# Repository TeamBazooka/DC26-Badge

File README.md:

# DC26 Team Bazooka

Figure it out

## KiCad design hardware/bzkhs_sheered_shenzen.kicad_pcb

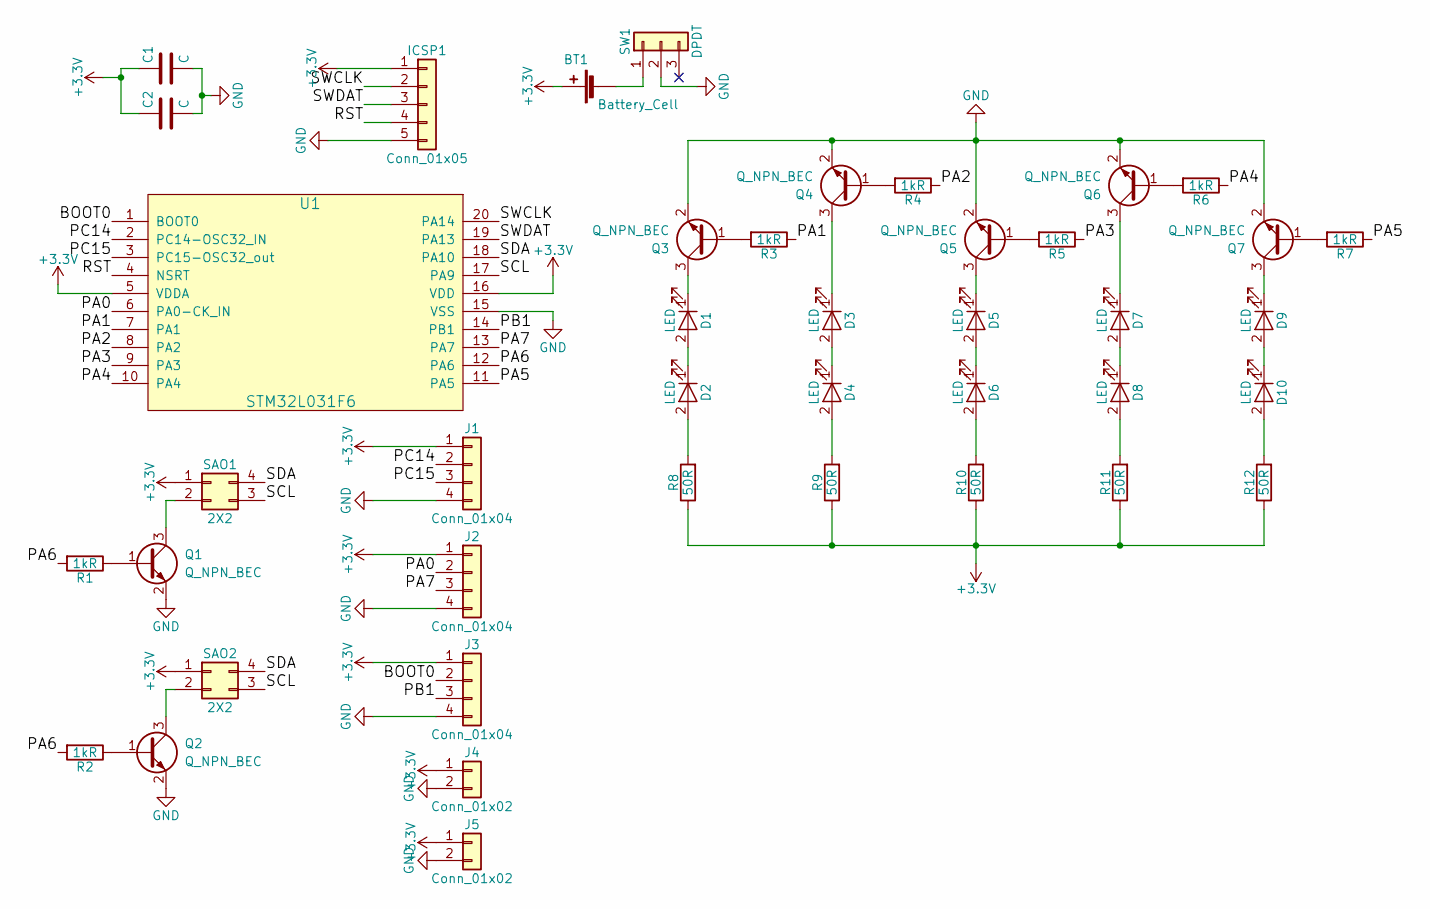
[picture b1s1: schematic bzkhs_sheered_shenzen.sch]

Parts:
BT1: Battery_Cell; aaa
C1, C2: C; C_0805
D1, D2, D3, D4, D5, D6, D7, D8, D9, D10: LED
ICSP1: Conn_01x05; 1X05_LOCK_LONGPADS
J1, J2, J3: Conn_01x04; 1X04_LONGPADS
J4, J5: Conn_01x02; 1X02_LONGPADS
Q1, Q2, Q3, Q4, Q5, Q6, Q7: Q_NPN_BEC; SOT23-3
R1, R2, R3, R4, R5, R6, R7: 1kR; R_0805
R8, R9, R10, R11, R12: 50R; R_0805
SAO1, SAO2: 2X2; Pin_Header_Straight_2x02_Pitch2.54mm
SW1: DPDT; JS202011JAQN
U1: STM32L031F6; TSSOP-20_4.4x6.5mm_Pitch0.65mm

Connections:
+3V3: BT1.1 (+), C1.1, C2.1, ICSP1.1, J1.1, J2.1, J3.1, J4.1, J5.1, R8.1, R9.1, R10.1, R11.1, R12.1, SAO1.1, SAO2.1, U1.5 (VDDA), U1.16 (VDD)
/BOOT0: J3.2, U1.1 (BOOT0)
/PA0: J2.2, U1.6 (PA0-CK_IN)
/PA1: R3.1, U1.7 (PA1)
/PA2: R4.1, U1.8 (PA2)
/PA3: R5.1, U1.9 (PA3)
/PA4: R6.1, U1.10 (PA4)
/PA5: R7.1, U1.11 (PA5)
/PA6: R1.2, R2.2, U1.12 (PA6)
/PA7: J2.3, U1.13 (PA7)
/PB1: J3.3, U1.14 (PB1)
/PC14: J1.2, U1.2 (PC14-OSC32_IN)
/PC15: J1.3, U1.3 (PC15-OSC32_out)
/RST: ICSP1.4, U1.4 (NSRT)
/SCL: SAO1.3, SAO2.3, U1.17 (PA9)
/SDA: SAO1.4, SAO2.4, U1.18 (PA10)
/SWCLK: ICSP1.2, U1.20 (PA14)
/SWDAT: ICSP1.3, U1.19 (PA13)
GND: C1.2, C2.2, ICSP1.5, J1.4, J2.4, J3.4, J4.2, J5.2, Q1.2 (E), Q2.2 (E), Q3.2 (E), Q4.2 (E), Q5.2 (E), Q6.2 (E), Q7.2 (E), SW1.2, U1.15 (VSS)
unnamed: BT1.2 (-), SW1.1
unnamed: D1.1 (K), Q3.3 (C)
unnamed: D1.2 (A), D2.1 (K)
unnamed: D2.2 (A), R8.2
unnamed: D3.1 (K), Q4.3 (C)
unnamed: D3.2 (A), D4.1 (K)
unnamed: D4.2 (A), R9.2
unnamed: D5.1 (K), Q5.3 (C)
unnamed: D5.2 (A), D6.1 (K)
unnamed: D6.2 (A), R10.2
unnamed: D7.1 (K), Q6.3 (C)
unnamed: D7.2 (A), D8.1 (K)
unnamed: D8.2 (A), R11.2
unnamed: D9.1 (K), Q7.3 (C)
unnamed: D9.2 (A), D10.1 (K)
unnamed: D10.2 (A), R12.2
unnamed: Q1.1 (B), R1.1
unnamed: Q1.3 (C), SAO1.2
unnamed: Q2.1 (B), R2.1
unnamed: Q2.3 (C), SAO2.2
unnamed: Q3.1 (B), R3.2
unnamed: Q4.1 (B), R4.2
unnamed: Q5.1 (B), R5.2
unnamed: Q6.1 (B), R6.2
unnamed: Q7.1 (B), R7.2

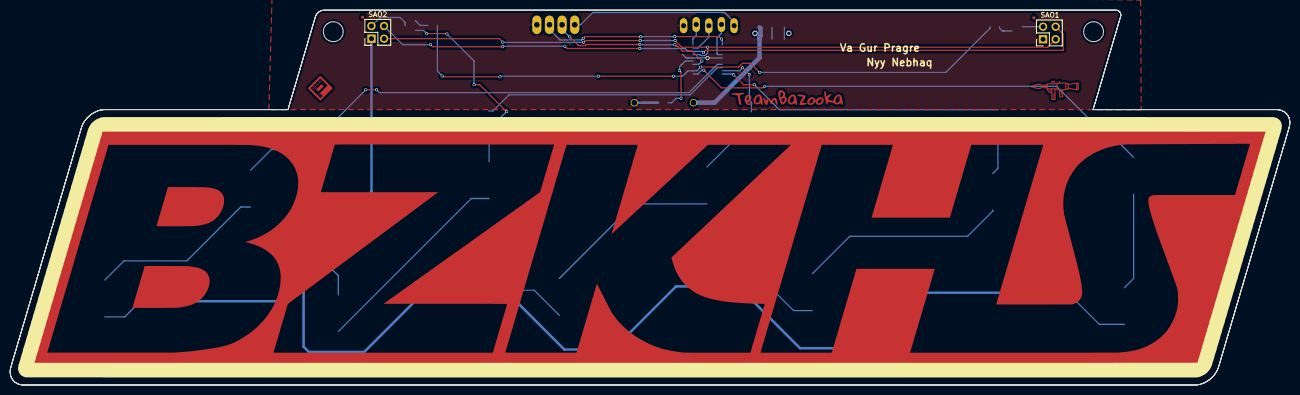
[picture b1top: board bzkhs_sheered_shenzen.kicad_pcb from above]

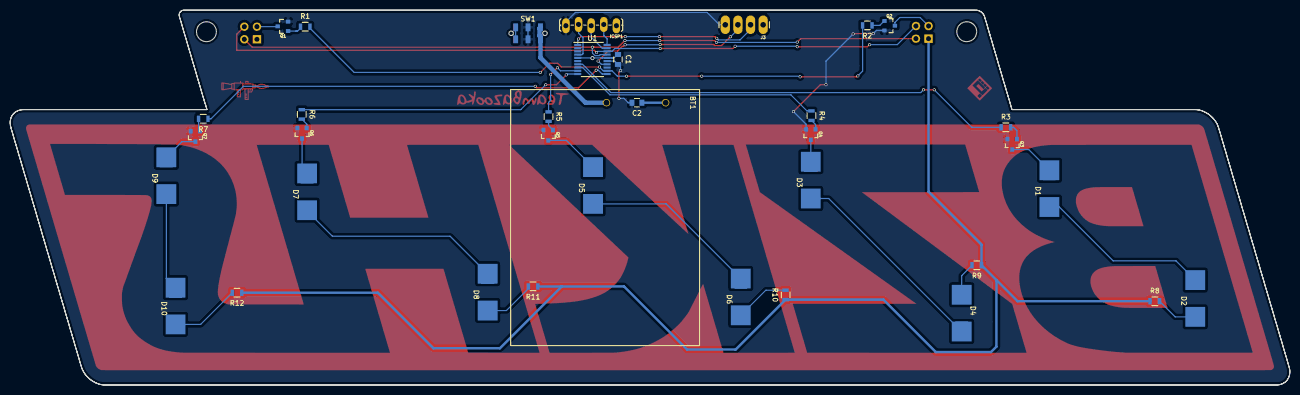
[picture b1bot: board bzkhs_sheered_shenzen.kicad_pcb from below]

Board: 2 copper layers, 257.5 x 75.4 mm, 40 parts (36 on the bottom side), 40 nets.

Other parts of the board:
F1, F1#2: Fiducial; FIDUCIAL-MICRO

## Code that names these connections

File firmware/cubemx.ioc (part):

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Mcu.Name=STM32L031F(4-6)Px
Mcu.Package=TSSOP20
Mcu.UserName=STM32L031F6Px
PA1.GPIOParameters=GPIO_Speed,PinState,GPIO_PuPd,GPIO_Label,GPIO_ModeDefaultOutputPP
PA1.GPIO_Label=LED_B
PA1.GPIO_ModeDefaultOutputPP=GPIO_MODE_OUTPUT_PP
PA1.GPIO_PuPd=GPIO_NOPULL
PA1.GPIO_Speed=GPIO_SPEED_FREQ_LOW
PA1.PinState=GPIO_PIN_SET
PA1.Signal=GPIO_Output
PA10.Signal=I2C1_SDA
PA13.Signal=LPUART1_RX
PA14.Signal=LPUART1_TX
PA2.GPIOParameters=GPIO_Speed,PinState,GPIO_PuPd,GPIO_Label,GPIO_ModeDefaultOutputPP
PA2.GPIO_Label=LED_Z
PA2.GPIO_ModeDefaultOutputPP=GPIO_MODE_OUTPUT_PP
PA2.GPIO_PuPd=GPIO_NOPULL
PA2.GPIO_Speed=GPIO_SPEED_FREQ_LOW
PA2.PinState=GPIO_PIN_SET
PA2.Signal=GPIO_Output
PA3.GPIOParameters=GPIO_Speed,PinState,GPIO_PuPd,GPIO_Label,GPIO_ModeDefaultOutputPP
PA3.GPIO_Label=LED_K
PA3.GPIO_ModeDefaultOutputPP=GPIO_MODE_OUTPUT_PP
PA3.GPIO_PuPd=GPIO_NOPULL
PA3.GPIO_Speed=GPIO_SPEED_FREQ_LOW
PA3.PinState=GPIO_PIN_SET
PA3.Signal=GPIO_Output
PA4.GPIOParameters=GPIO_Speed,PinState,GPIO_PuPd,GPIO_Label,GPIO_ModeDefaultOutputPP
PA4.GPIO_Label=LED_H
PA4.GPIO_ModeDefaultOutputPP=GPIO_MODE_OUTPUT_PP
PA4.GPIO_PuPd=GPIO_NOPULL
PA4.GPIO_Speed=GPIO_SPEED_FREQ_LOW
PA4.PinState=GPIO_PIN_SET
PA4.Signal=GPIO_Output
PA5.GPIOParameters=GPIO_Speed,PinState,GPIO_PuPd,GPIO_Label,GPIO_ModeDefaultOutputPP
PA5.GPIO_Label=LED_S
PA5.GPIO_ModeDefaultOutputPP=GPIO_MODE_OUTPUT_PP
PA5.GPIO_PuPd=GPIO_NOPULL
PA5.GPIO_Speed=GPIO_SPEED_FREQ_LOW
PA5.PinState=GPIO_PIN_SET
PA5.Signal=GPIO_Output
PA6.GPIOParameters=GPIO_Speed,PinState,GPIO_PuPd,GPIO_Label,GPIO_ModeDefaultOutputPP
PA6.GPIO_Label=SW_SAO
PA6.GPIO_ModeDefaultOutputPP=GPIO_MODE_OUTPUT_PP
PA6.GPIO_PuPd=GPIO_NOPULL
PA6.GPIO_Speed=GPIO_SPEED_FREQ_LOW
PA6.PinState=GPIO_PIN_SET
PA6.Signal=GPIO_Output
PA9.Signal=I2C1_SCL
RCC.HSE_VALUE=8000000
RCC.SYSCLKFreq_VALUE=16000000
RCC.SYSCLKSource=RCC_SYSCLKSOURCE_HSI
board=custom

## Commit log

2018-07-23 ignore built files
2018-07-23 All placed
2018-07-23 Finished
2018-07-23 Refactor entrypoint
2018-07-23 blink all lines
2018-07-23 Automatically download and install toolchain to build firmware
2018-07-23 Add animations and "random" function
2018-07-23 get arm toolschain instead of platformio
